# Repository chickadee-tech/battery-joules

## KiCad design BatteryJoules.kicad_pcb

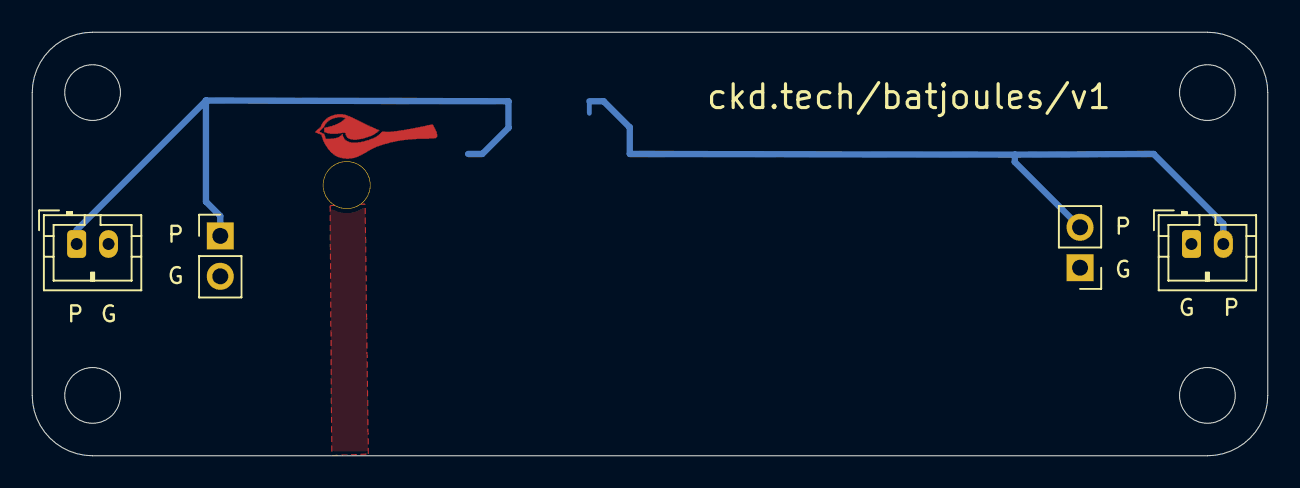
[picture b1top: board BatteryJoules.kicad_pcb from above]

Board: 2 copper layers, 77.6 x 26.6 mm, 5 parts (1 on the bottom side), 3 nets.

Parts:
J1, J5: Conn_01x02_Male; JST_PH_B2B-PH-K_1x02_P2.00mm_Vertical
J2, J4: Conn_01x02_Female; PinHeader_1x02_P2.54mm_Vertical
J3: Conn_01x05_Male; PinHeader_1x05_P2.54mm_Vertical_SMD_Pin1Left

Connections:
+5V: J1.1, J2.1, J3.4, J3.5
GND: J1.2, J2.2, J3.3, J4.1, J5.1
VBUS: J3.1, J3.2, J4.2, J5.2

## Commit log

2020-03-06 Initial version. v1
